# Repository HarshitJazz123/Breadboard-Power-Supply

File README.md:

# Breadboard-Power-Supply
A custom 2 layer pcb , power supply board which fits directly onto breadboard 
# Breadboard Power Supply PCB

A 2-layer breadboard power supply board designed in KiCad.

## Specs
- Input: 12 V DC via barrel jack, with on/off switch
- Outputs: two independent output headers, each jumper-selectable between 3.3 V and 5 V
- 3.3 V rail: LM317 adjustable regulator (R1 = 240 ohm, R2 = 390 ohm, about 3.28 V)
- 5 V rail: LM7805 fixed regulator
- Power-on indicator LED
- Output connectors: 2-pin headers and screw terminals for the breadboard
- Current: regulators are rated 1.5 A, but at 12 V input each one dissipates 7-8.7 W per amp, so a heatsink is needed above roughly 100-150 mA

## Known limitations
- No reverse-polarity protection or fuse
- Not yet fabricated or tested
  
## Status
Schematic, 2-layer board layout and 3D model are complete. Final DRC cleanup is in progress.

## Files
- `kicad/` : KiCad project (schematic and PCB)
- `docs/schematic.pdf` : schematic
- `docs/pcb_3d.png` : 3D render

Built with KiCad.

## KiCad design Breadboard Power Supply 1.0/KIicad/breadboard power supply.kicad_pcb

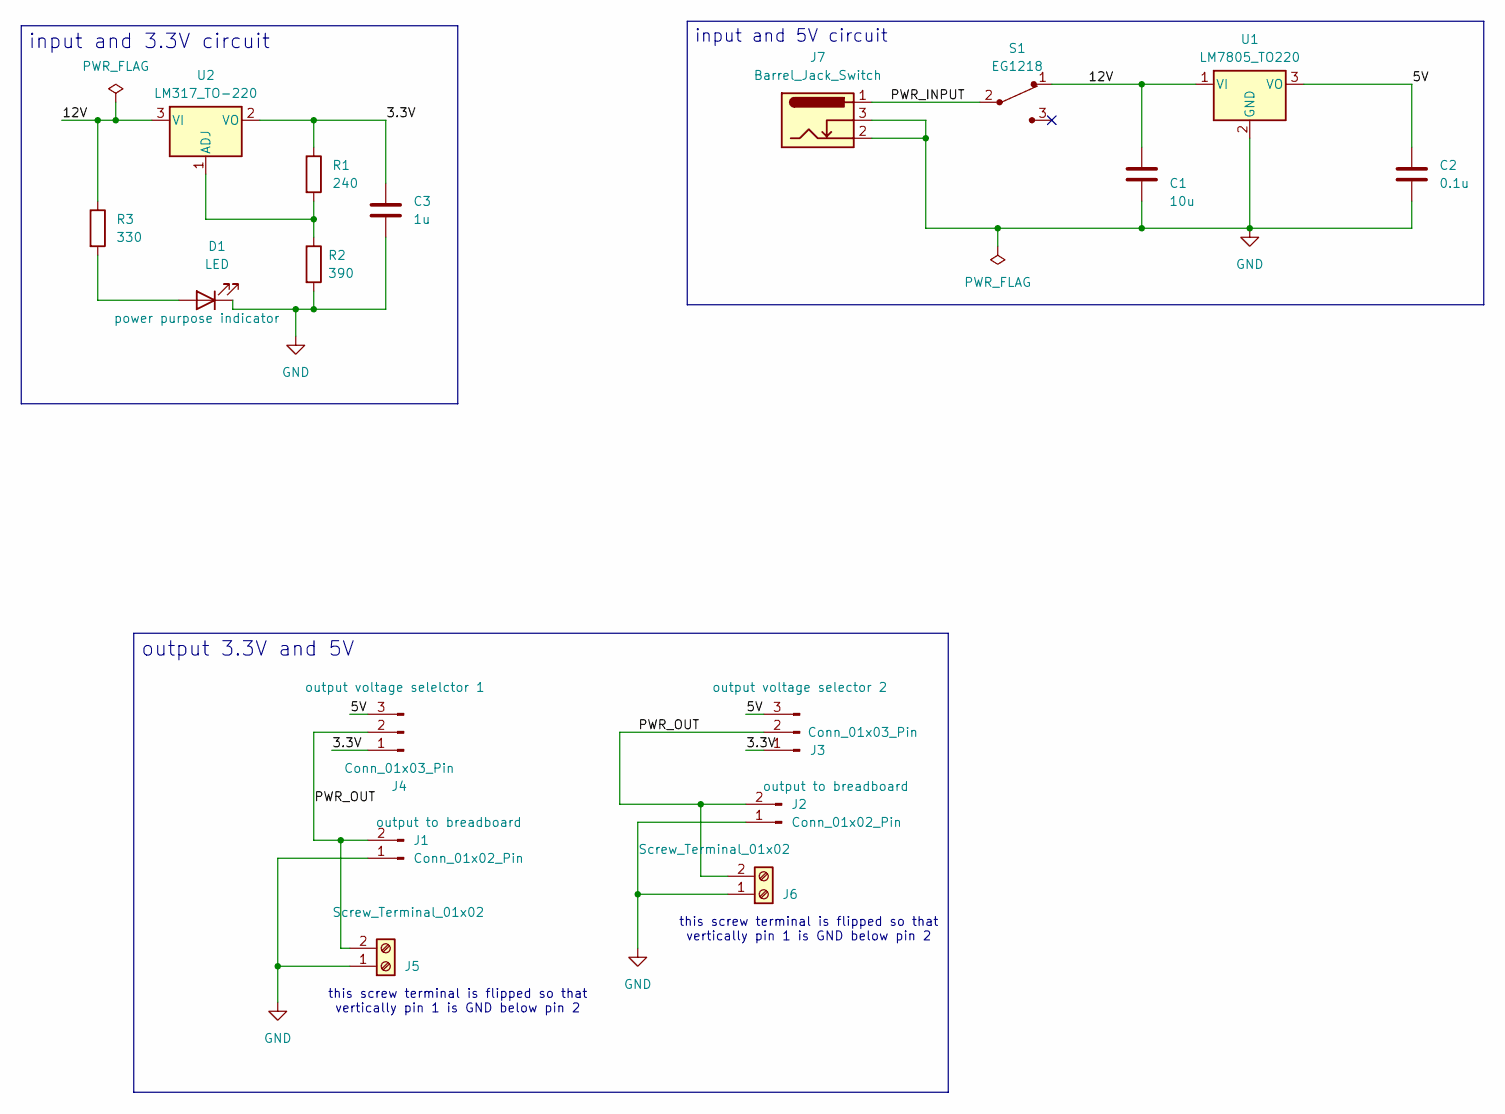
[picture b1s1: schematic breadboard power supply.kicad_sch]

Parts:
C1: 10u; C_Disc_D3.0mm_W1.6mm_P2.50mm
C2: 0.1u; C_Disc_D3.0mm_W1.6mm_P2.50mm
C3: 1u; C_Disc_D3.0mm_W1.6mm_P2.50mm
D1: LED; LED_D5.0mm
J1, J2: Conn_01x02_Pin; PinHeader_1x02_P2.54mm_Vertical
J3, J4: Conn_01x03_Pin; PinHeader_1x03_P2.54mm_Vertical
J5, J6: Screw_Terminal_01x02; Altech_AK100_1x02_P5.00mm
J7: Barrel_Jack_Switch; BarrelJack_GCT_DCJ200-10-A_Horizontal
R1: 240; R_Axial_DIN0204_L3.6mm_D1.6mm_P7.62mm_Horizontal
R2: 390; R_Axial_DIN0204_L3.6mm_D1.6mm_P7.62mm_Horizontal
R3: 330; R_Axial_DIN0204_L3.6mm_D1.6mm_P7.62mm_Horizontal
S1: EG1218; Switch_Slide_11.6x4mm_EG1218; MPN EG1218; Digi-Key_PN EG1903-ND
U1: LM7805_TO220; TO-220-3_Vertical
U2: LM317_TO-220; TO-220-3_Vertical

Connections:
/3.3V: C3.1, J3.1, J4.1, R1.1, U2.2 (VO)
/5V: C2.1, J3.3, J4.3, U1.3 (VO)
/12V: C1.1, R3.1, S1.1, U1.1 (VI), U2.3 (VI)
/PWR_INPUT: J7.1, S1.2
/PWR_OUT: J1.2, J2.2, J3.2, J4.2, J5.2, J6.2
GND: C1.2, C2.2, C3.2, D1.1 (K), J1.1, J2.1, J5.1, J6.1, J7.2, J7.3, R2.2, U1.2 (GND)
unnamed: D1.2 (A), R3.2
unnamed: R1.2, R2.1, U2.1 (ADJ)

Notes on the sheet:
this screw terminal is flipped so that vertically pin 1 is GND below pin 2
input and 3.3V circuit
output 3.3V and 5V
input and 5V circuit

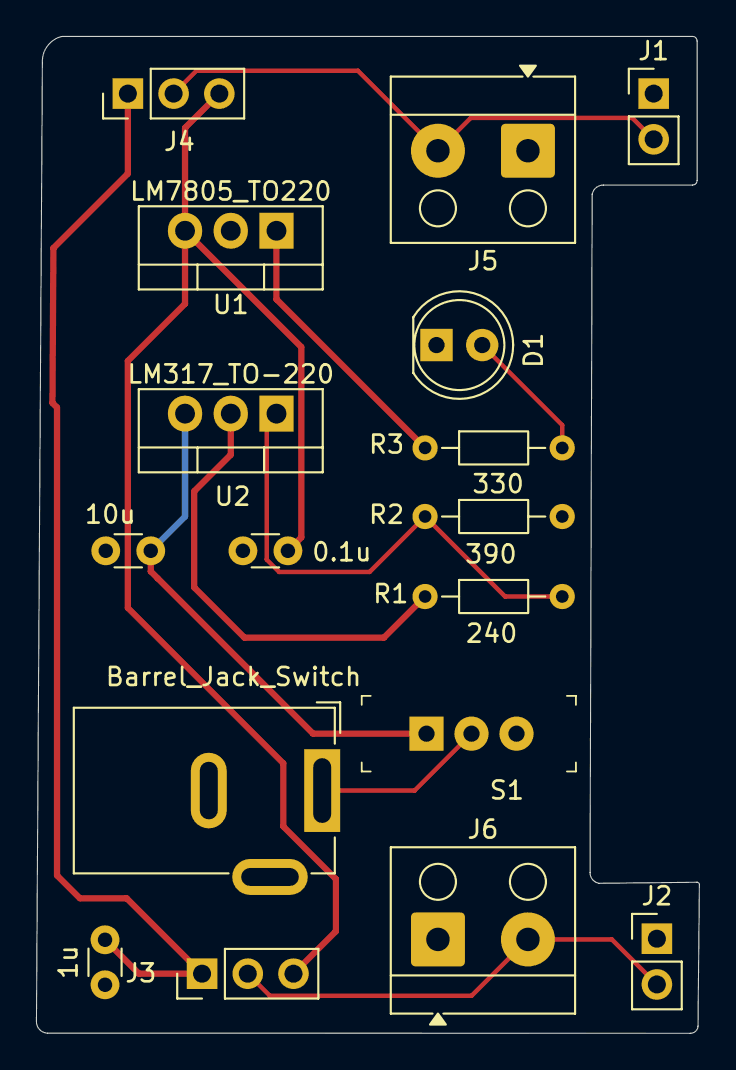
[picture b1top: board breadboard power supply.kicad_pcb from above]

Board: 2 copper layers, 36.8 x 55.4 mm, 17 parts (0 on the bottom side), 8 nets.
